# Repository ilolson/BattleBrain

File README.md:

# BattleBrain
Microcontroller hub for battlebot components.
3D Printing Club

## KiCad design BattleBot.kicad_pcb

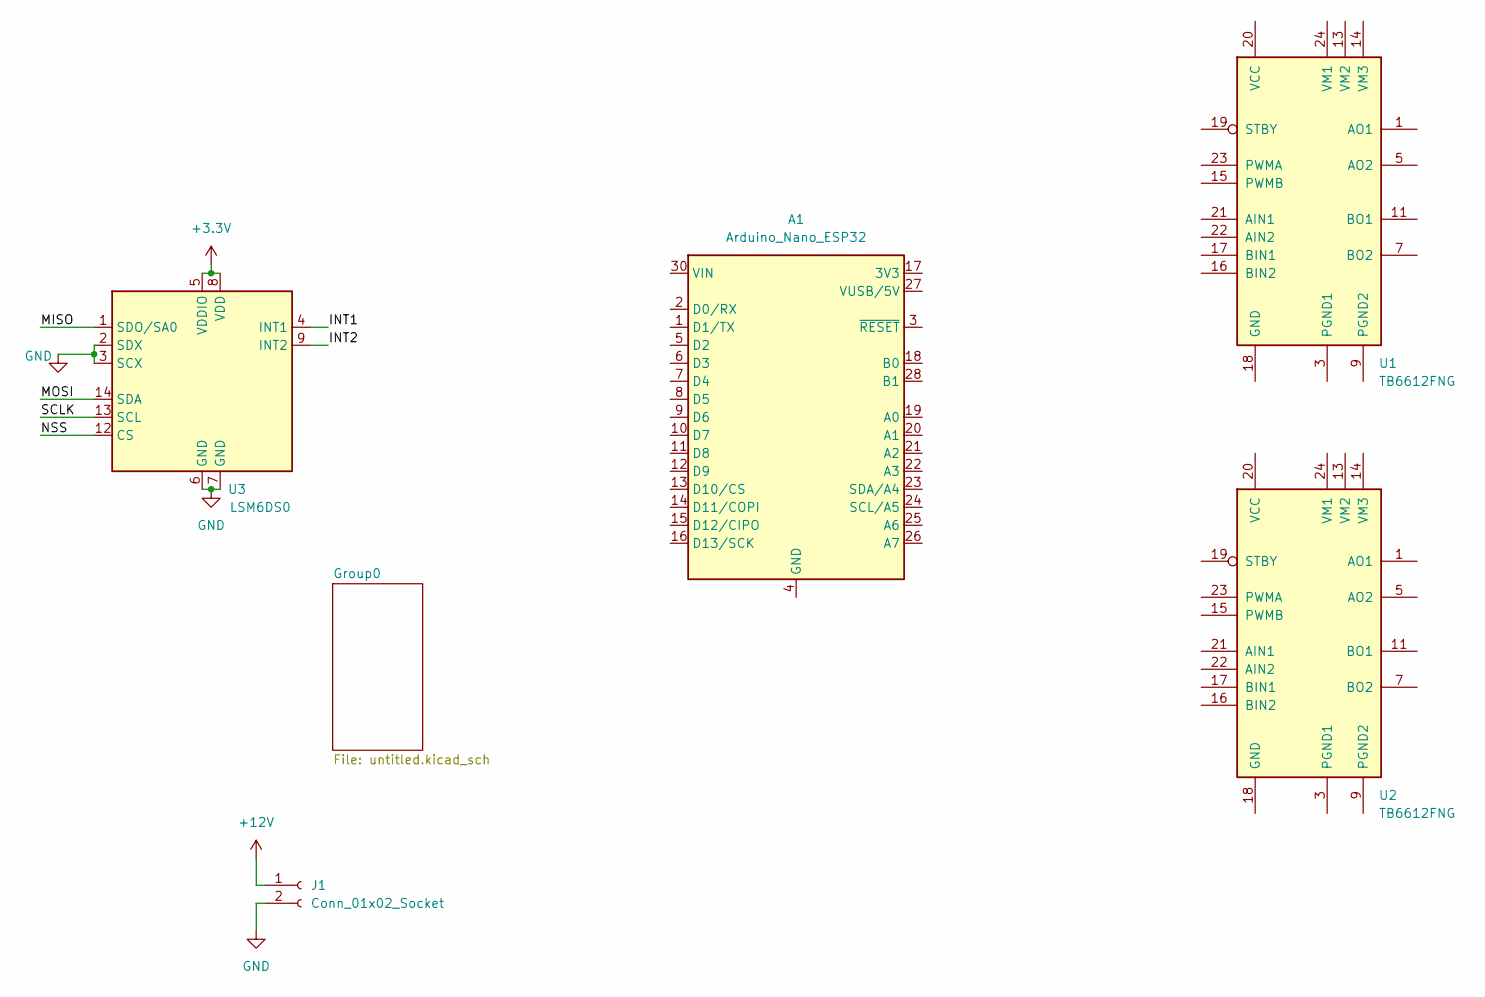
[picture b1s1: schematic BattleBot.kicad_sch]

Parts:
A1: Arduino_Nano_ESP32; Arduino_Nano
J1: Conn_01x02_Socket; AMASS_XT60PW-F_1x02_P7.20mm_Horizontal
U1, U2: TB6612FNG; SSOP-24_5.3x8.2mm_P0.65mm
U3: LSM6DS0; LGA-14_3x2.5mm_P0.5mm_LayoutBorder3x4y

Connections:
+3.3V: U3.5 (VDDIO), U3.8 (VDD)
+12V: J1.1
/INT1: U3.4 (INT1)
/INT2: U3.9 (INT2)
/MISO: U3.1 (SDO/SA0)
/MOSI: U3.14 (SDA)
/NSS: U3.12 (CS)
/SCLK: U3.13 (SCL)
GND: J1.2, U3.2 (SDX), U3.3 (SCX), U3.6 (GND), U3.7 (GND)
unnamed: A1.4 (GND), A1.29 (GND)
unnamed: U1.1 (AO1), U1.2 (AO1)
unnamed: U1.5 (AO2), U1.6 (AO2)
unnamed: U1.11 (BO1), U1.12 (BO1)
unnamed: U1.7 (BO2), U1.8 (BO2)
unnamed: U1.3 (PGND1), U1.4 (PGND1)
unnamed: U1.9 (PGND2), U1.10 (PGND2)
unnamed: U2.1 (AO1), U2.2 (AO1)
unnamed: U2.5 (AO2), U2.6 (AO2)
unnamed: U2.11 (BO1), U2.12 (BO1)
unnamed: U2.7 (BO2), U2.8 (BO2)
unnamed: U2.3 (PGND1), U2.4 (PGND1)
unnamed: U2.9 (PGND2), U2.10 (PGND2)

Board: 2 copper layers, 5 parts (2 on the bottom side), 15 nets, no tracks yet.

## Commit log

2025-03-06 init
